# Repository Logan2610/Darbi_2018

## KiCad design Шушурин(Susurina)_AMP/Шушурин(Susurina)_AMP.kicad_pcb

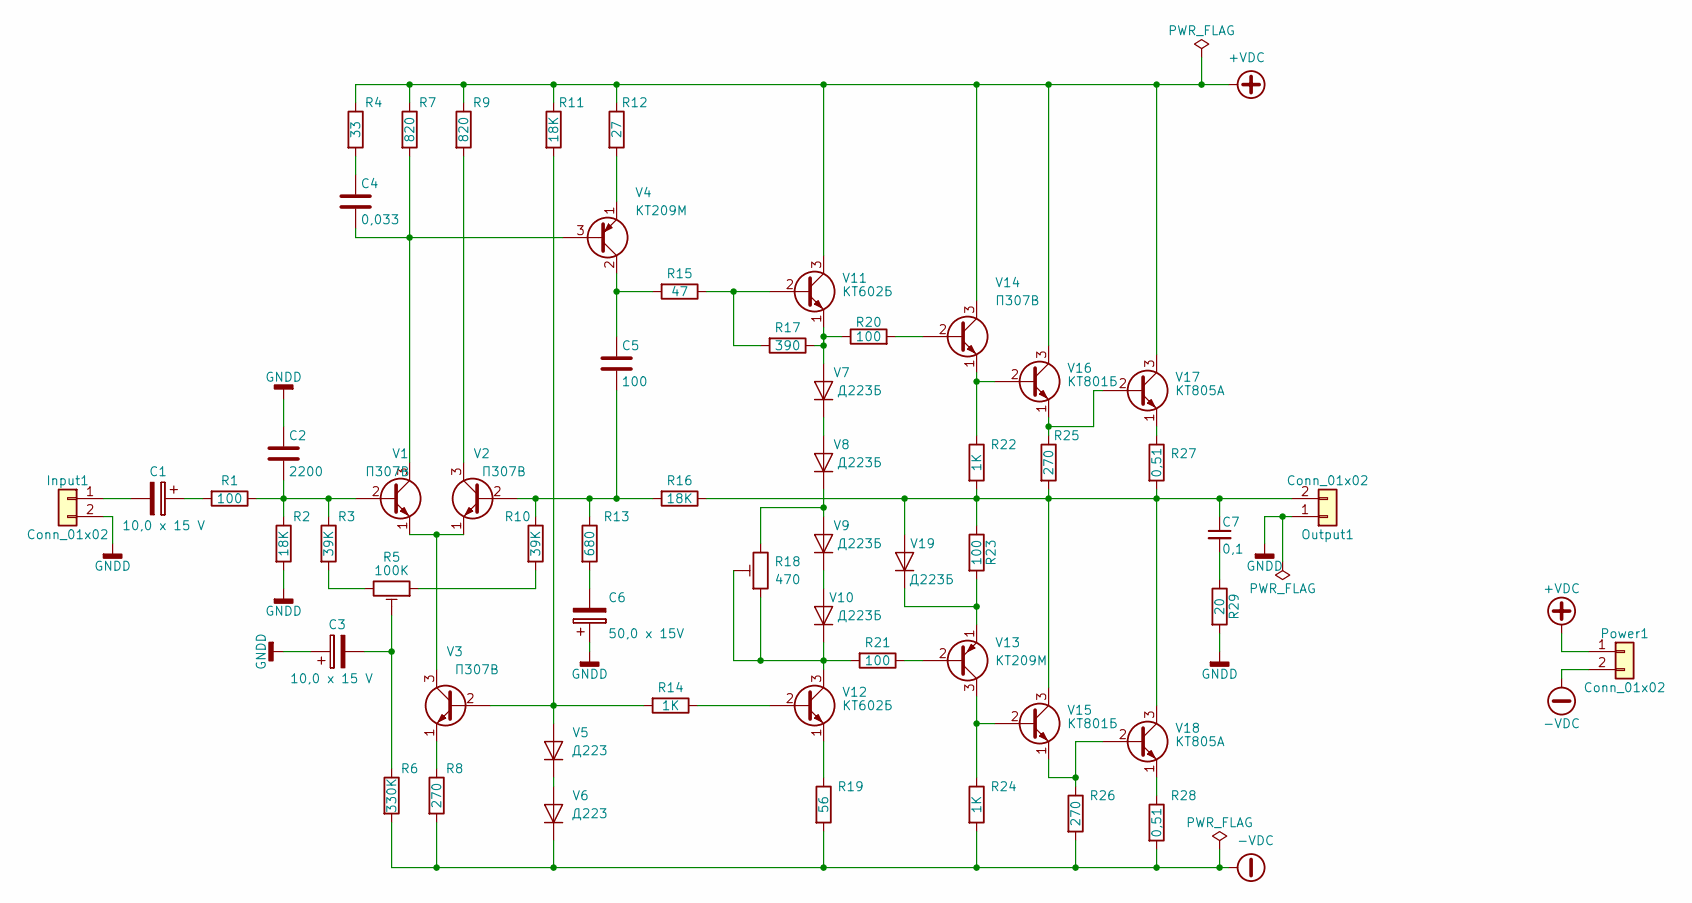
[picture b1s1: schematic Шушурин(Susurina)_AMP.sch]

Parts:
C1, C3: 10,0 x 15 V; CP_Radial_D10.0mm_P5.00mm
C2: 2200; CP_Radial_D10.0mm_P5.00mm
C4: 0,033; CP_Radial_D10.0mm_P5.00mm
C5: 100; CP_Radial_D10.0mm_P5.00mm
C6: 50,0 x 15V; CP_Radial_D10.0mm_P5.00mm
C7: 0,1; C_Rect_L33.0mm_W13.0mm_P27.50mm_MKS4
Input1: Conn_01x02; TerminalBlock_Altech_AK300-2_P5.00mm
Output1: Conn_01x02; TerminalBlock_Altech_AK300-2_P5.00mm
Power1: Conn_01x02; Banana_Jack_2Pin
R1, R20, R21, R23: 100; R_Axial_DIN0207_L6.3mm_D2.5mm_P15.24mm_Horizontal
R2, R11, R16: 18K; R_Axial_DIN0207_L6.3mm_D2.5mm_P15.24mm_Horizontal
R3, R10: 39K; R_Axial_DIN0207_L6.3mm_D2.5mm_P15.24mm_Horizontal
R4: 33; R_Axial_DIN0207_L6.3mm_D2.5mm_P15.24mm_Horizontal
R5: 100K; TRIM_3296Y-1-202LF
R6: 330K; R_Axial_DIN0207_L6.3mm_D2.5mm_P15.24mm_Horizontal
R7, R9: 820; R_Axial_DIN0207_L6.3mm_D2.5mm_P15.24mm_Horizontal
R8, R25, R26: 270; R_Axial_DIN0207_L6.3mm_D2.5mm_P15.24mm_Horizontal
R12: 27; R_Axial_DIN0207_L6.3mm_D2.5mm_P15.24mm_Horizontal
R13: 680; R_Axial_DIN0207_L6.3mm_D2.5mm_P15.24mm_Horizontal
R14, R22, R24: 1K; R_Axial_DIN0207_L6.3mm_D2.5mm_P15.24mm_Horizontal
R15: 47; R_Axial_DIN0207_L6.3mm_D2.5mm_P15.24mm_Horizontal
R17: 390; R_Axial_DIN0207_L6.3mm_D2.5mm_P15.24mm_Horizontal
R18: 470; TRIM_3296Y-1-202LF
R19: 56; R_Axial_DIN0207_L6.3mm_D2.5mm_P15.24mm_Horizontal
R27, R28: 0,51; R_Axial_DIN0207_L6.3mm_D2.5mm_P15.24mm_Horizontal
R29: 20; R_Axial_DIN0207_L6.3mm_D2.5mm_P15.24mm_Horizontal
V1, V2, V3, V14: П307В; OldSowjetaera_Transistor_Type-II_SmallPads
V4, V13: KT209M; OldSowjetaera_Transistor_Type-I_SmallPads
V5, V6: Д223; D_DO-27_P15.24mm_Horizontal
V7, V8, V9, V10, V19: Д223Б; D_DO-27_P15.24mm_Horizontal
V11, V12: KT602Б; Crystal_HC35-U
V15, V16: KT801Б; Crystal_HC35-U
V17, V18: KT805A; PINHEAD1-3

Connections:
+VDC: Power1.1, R4.1, R7.1, R9.1, R11.1, R12.1, V11.3 (C), V14.3 (C), V16.3 (C), V17.3 (C)
-VDC: Power1.2, R6.2, R8.2, R19.2, R24.2, R26.2, R28.2, V6.1 (K)
GNDD: C2.1, C3.1, C6.1, Input1.2, Output1.1, R2.2, R29.2
unnamed: C1.1, R1.2
unnamed: C1.2, Input1.1
unnamed: C2.2, R1.1, R2.1, R3.1, V1.2 (B)
unnamed: C3.2, R5.2, R6.1
unnamed: C4.1, R4.2
unnamed: C4.2, R7.2, V1.3 (C), V4.3 (B)
unnamed: C5.1, R15.2, V4.2 (C)
unnamed: C5.2, R10.1, R13.1, R16.2, V2.2 (B)
unnamed: C6.2, R13.2
unnamed: C7.1, Output1.2, R16.1, R22.2, R23.1, R25.2, R27.2, V15.3 (C), V18.3 (C), V19.2 (A)
unnamed: C7.2, R29.1
unnamed: R3.2, R5.3
unnamed: R8.1, V3.1 (E)
unnamed: R9.2, V2.3 (C)
unnamed: R5.1, R10.2
unnamed: R11.2, R14.2, V3.2 (B), V5.2 (A)
unnamed: R12.2, V4.1 (E)
unnamed: R14.1, V12.2 (B)
unnamed: R15.1, R17.2, V11.2 (B)
unnamed: R17.1, R20.1, V7.2 (A), V11.1 (E)
unnamed: R18.1, R18.2, R21.2, V10.1 (K), V12.3 (C)
unnamed: R18.3, V8.1 (K), V9.2 (A)
unnamed: R19.1, V12.1 (E)
unnamed: R20.2, V14.2 (B)
unnamed: R21.1, V13.2 (B)
unnamed: R22.1, V14.1 (E), V16.2 (B)
unnamed: R23.2, V13.1 (E), V19.1 (K)
unnamed: R24.1, V13.3 (C), V15.2 (B)
unnamed: R25.1, V16.1 (E), V17.2 (B)
unnamed: R26.1, V15.1 (E), V18.2 (B)
unnamed: R27.1, V17.1 (E)
unnamed: R28.1, V18.1 (E)
unnamed: V1.1 (E), V2.1 (E), V3.3 (C)
unnamed: V5.1 (K), V6.2 (A)
unnamed: V7.1 (K), V8.2 (A)
unnamed: V9.1 (K), V10.2 (A)

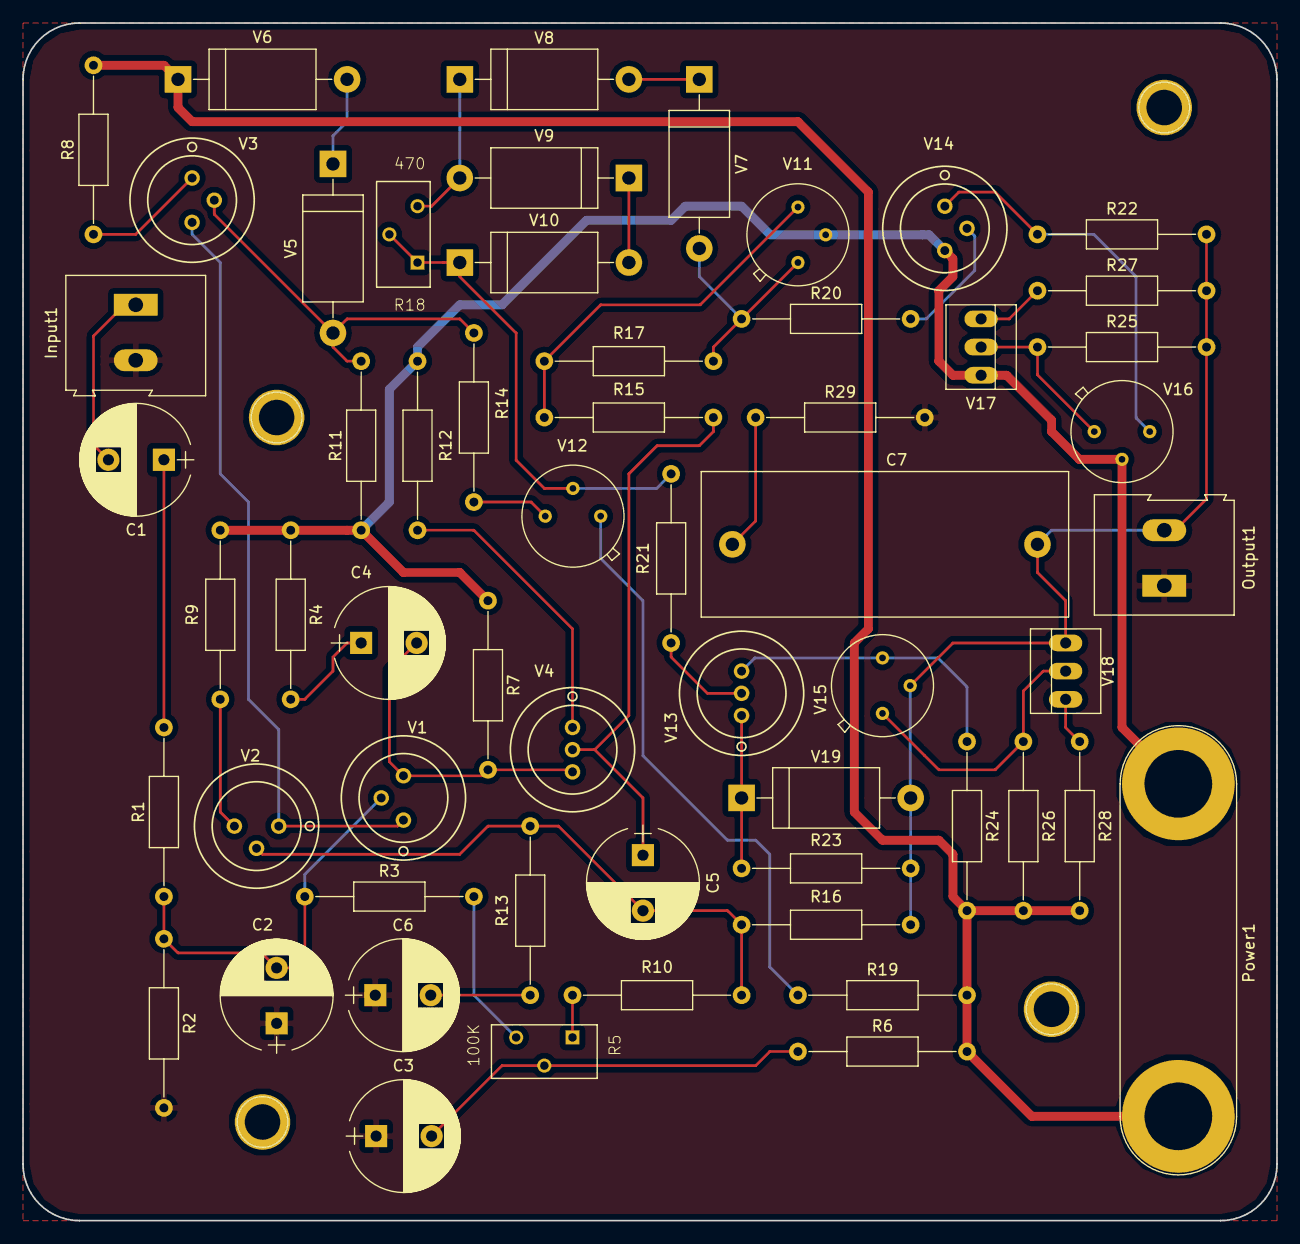
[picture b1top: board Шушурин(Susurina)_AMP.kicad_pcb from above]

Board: 2 copper layers, 113.0 x 108.0 mm, 58 parts (0 on the bottom side), 39 nets.

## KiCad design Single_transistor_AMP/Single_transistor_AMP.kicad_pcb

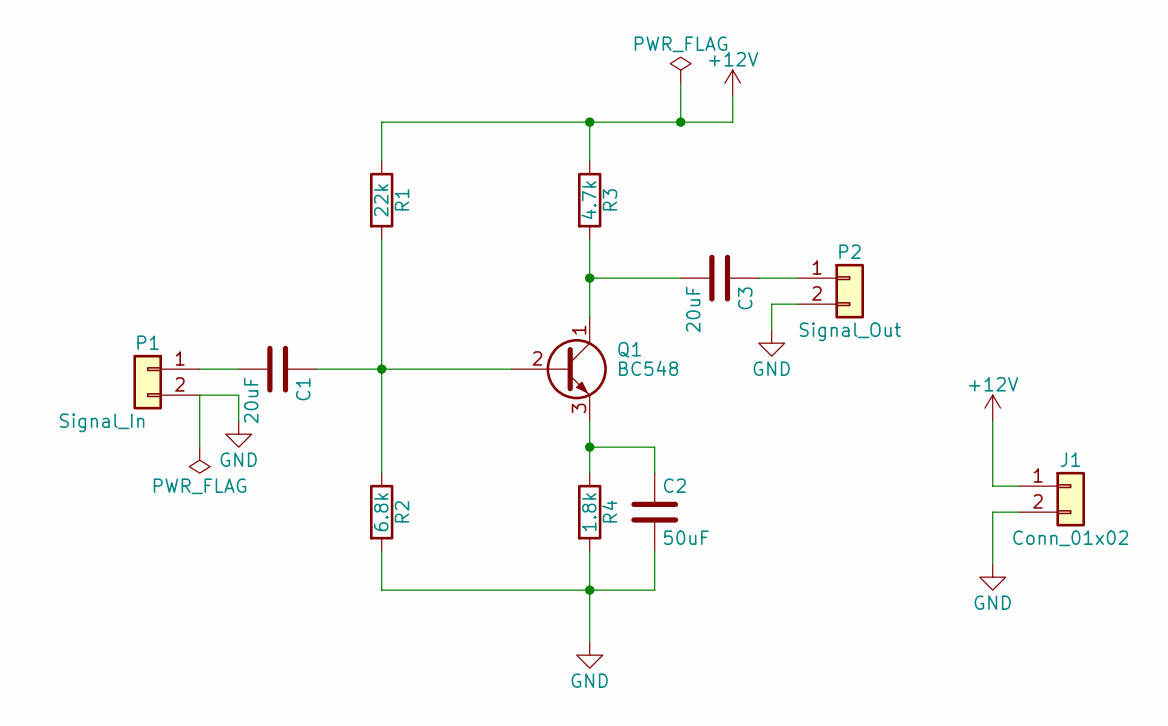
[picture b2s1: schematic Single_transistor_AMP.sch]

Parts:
C1, C3: 20uF; CP_Axial_L18.0mm_D8.0mm_P25.00mm_Horizontal
C2: 50uF; CP_Axial_L21.0mm_D8.0mm_P28.00mm_Horizontal
J1: Conn_01x02; Banana_Jack_2Pin
P1: Signal_In; TerminalBlock_Altech_AK300-2_P5.00mm
P2: Signal_Out; TerminalBlock_Altech_AK300-2_P5.00mm
Q1: BC548; TO-92_Molded_Narrow
R1: 22k; R_Axial_DIN0516_L15.5mm_D5.0mm_P20.32mm_Horizontal
R2: 6.8k; R_Axial_DIN0516_L15.5mm_D5.0mm_P20.32mm_Horizontal
R3: 4.7k; R_Axial_DIN0516_L15.5mm_D5.0mm_P20.32mm_Horizontal
R4: 1.8k; R_Axial_DIN0516_L15.5mm_D5.0mm_P20.32mm_Horizontal

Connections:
+12V: J1.1, R1.1, R3.1
GND: C2.2, J1.2, P1.2, P2.2, R2.2, R4.2
unnamed: C1.1, Q1.2 (B), R1.2, R2.1
unnamed: C1.2, P1.1
unnamed: C2.1, Q1.3 (E), R4.1
unnamed: C3.1, P2.1
unnamed: C3.2, Q1.1 (C), R3.2

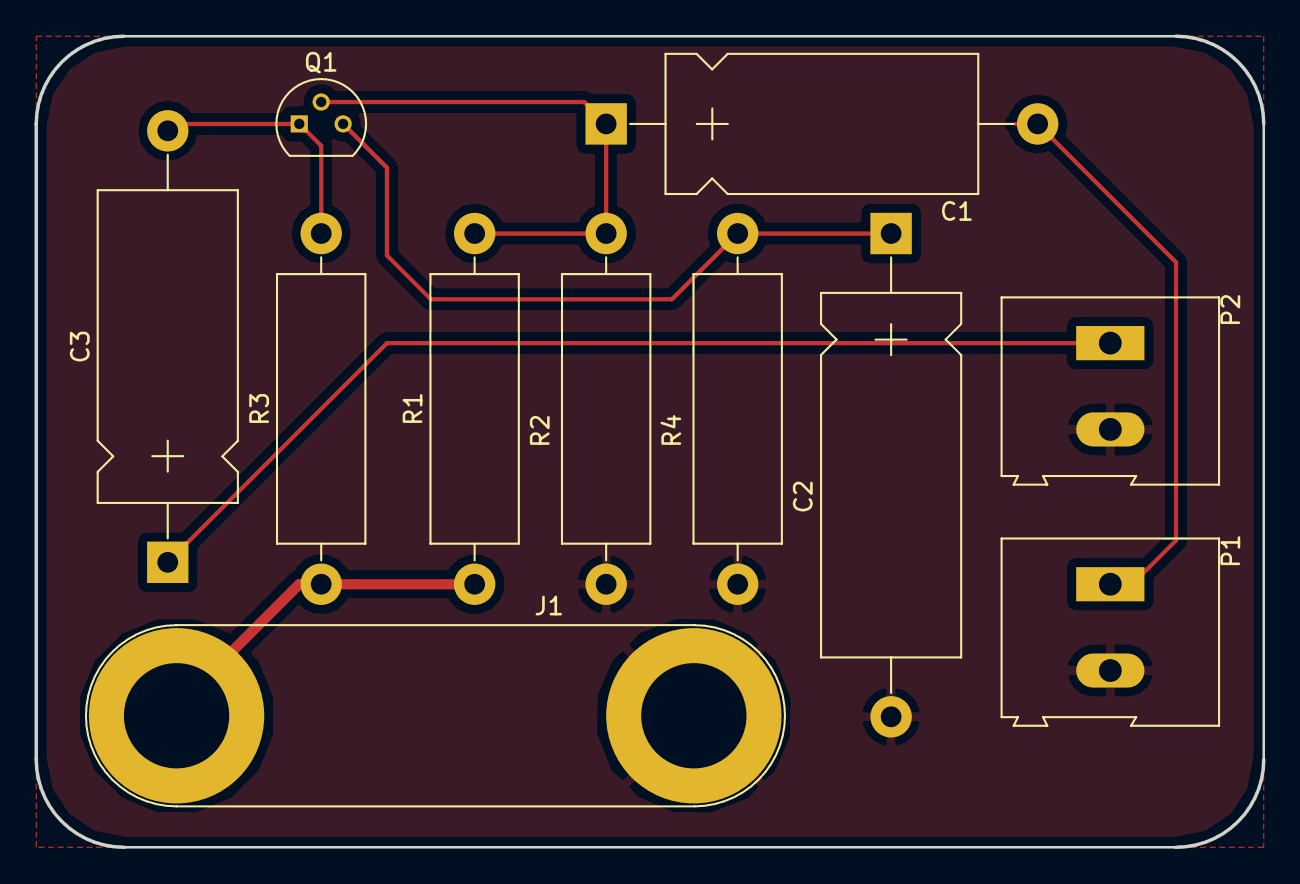
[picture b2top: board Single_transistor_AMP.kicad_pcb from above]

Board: 2 copper layers, 71.1 x 47.0 mm, 11 parts (0 on the bottom side), 7 nets.

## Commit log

2018-03-14 Tranzistori aizstati ar IC mikroshemu
2018-03-14 0.2
    Tranzistori BC548 tiek aizstati ar IC mikroshemu
    This reverts commit 3d703b0aae8bc0295c59cc91b30c956ba27862da.
2018-03-14 0.21
    Iekļauta pazaudētā bibliotēka
2018-03-15 1.0
    Shēmas komponentēm ir pievienoti footprinti un datulapa, kā arī izveidots netlist fails.
2018-03-22 1.0
    Tika izveidota un anoteta shema erori tika savesti kartiba tik cik vien varēja pievienojot klāt power_flagus
2018-03-29 0.22
2018-03-29 1.0
    Izveidota principālā baterijas shēma, kā arī izveidoti 5 baterijas holder footprinti.
2018-04-04 1.1
    Tiek izveidoti atbilstoši plates slāņu iestatījumi, kā arī tiek izveidots dizaina nosacījums ar vismaz 2 savienojuma grupām.
2018-04-05 1.2
    Izlabots autors.
    Tika noņemts lodēšanas pastas stencils.
    Tika noņemts tekstu, attēlu utml. iestatījums plates apakšpusē.
    Tika noņemts Eco1 un Eco2, jo plate netiks nodota recenzēšanai.
2018-04-11 1.4
    Izveidots PCB dizains, kā arī papildināta shēma
2018-05-08 1.7
    1.6 Tika dizainēta plate ar tās slāņiem.
    1.7 Tiek izveidoti gerber faili.
2018-05-08 1.8
    1. Izveidota atbilstoša BOM atskaite.
    2. Katram izmantotajam plates slānim izveidots SVG attēls.
2018-05-14 2.0
    Izveidota shēma,
    Pievienoti footprinti komponentēm,
    Daļēji izveidots plates dizains.
2018-06-11 5.0
    Gala darbs
